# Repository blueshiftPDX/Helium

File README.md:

Helium
======

Helium supercapacitor-powered portable wireless speaker

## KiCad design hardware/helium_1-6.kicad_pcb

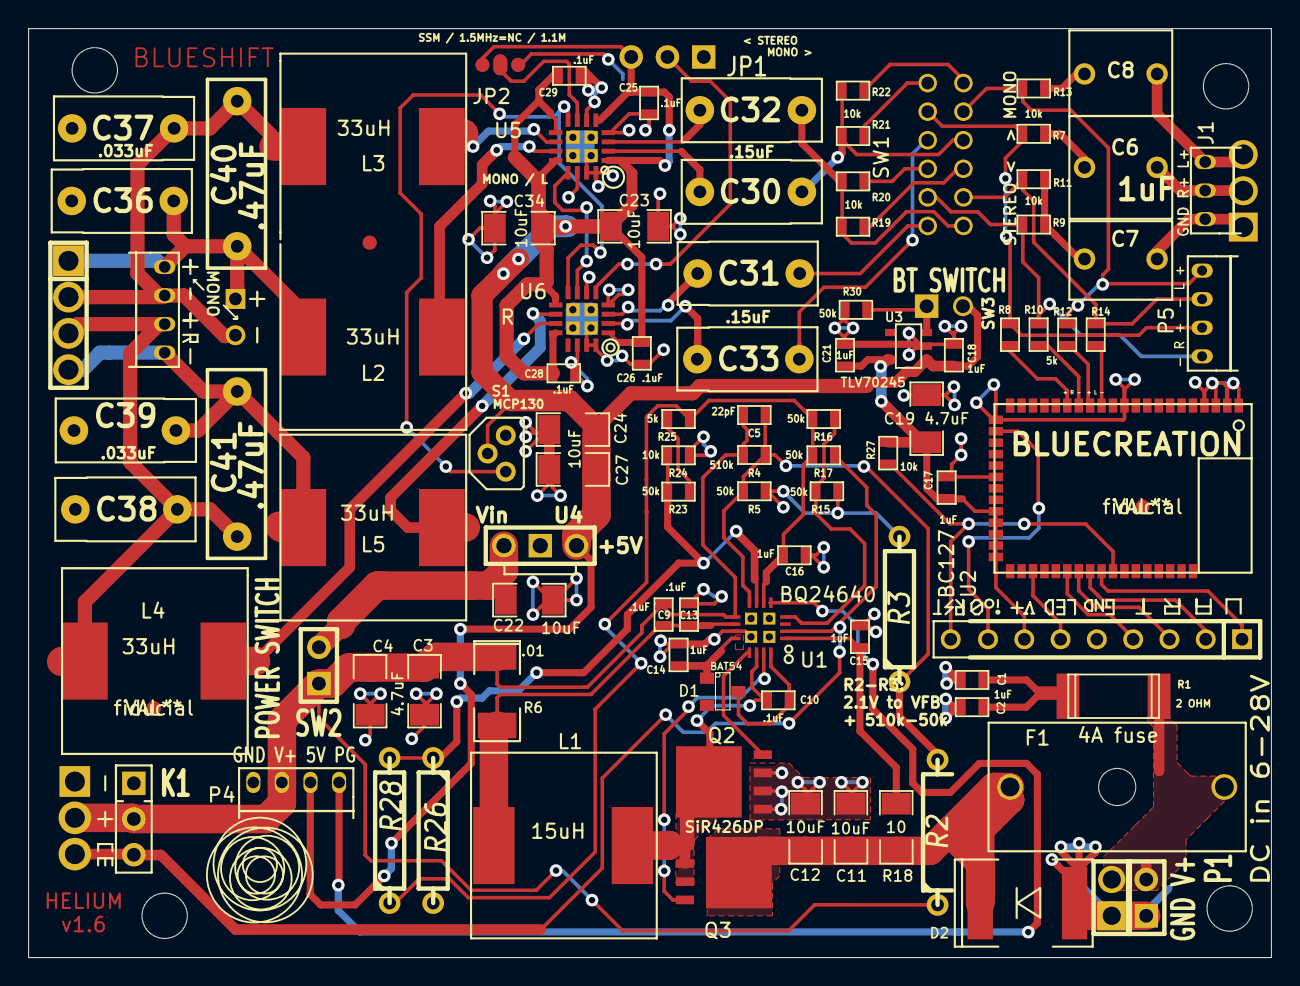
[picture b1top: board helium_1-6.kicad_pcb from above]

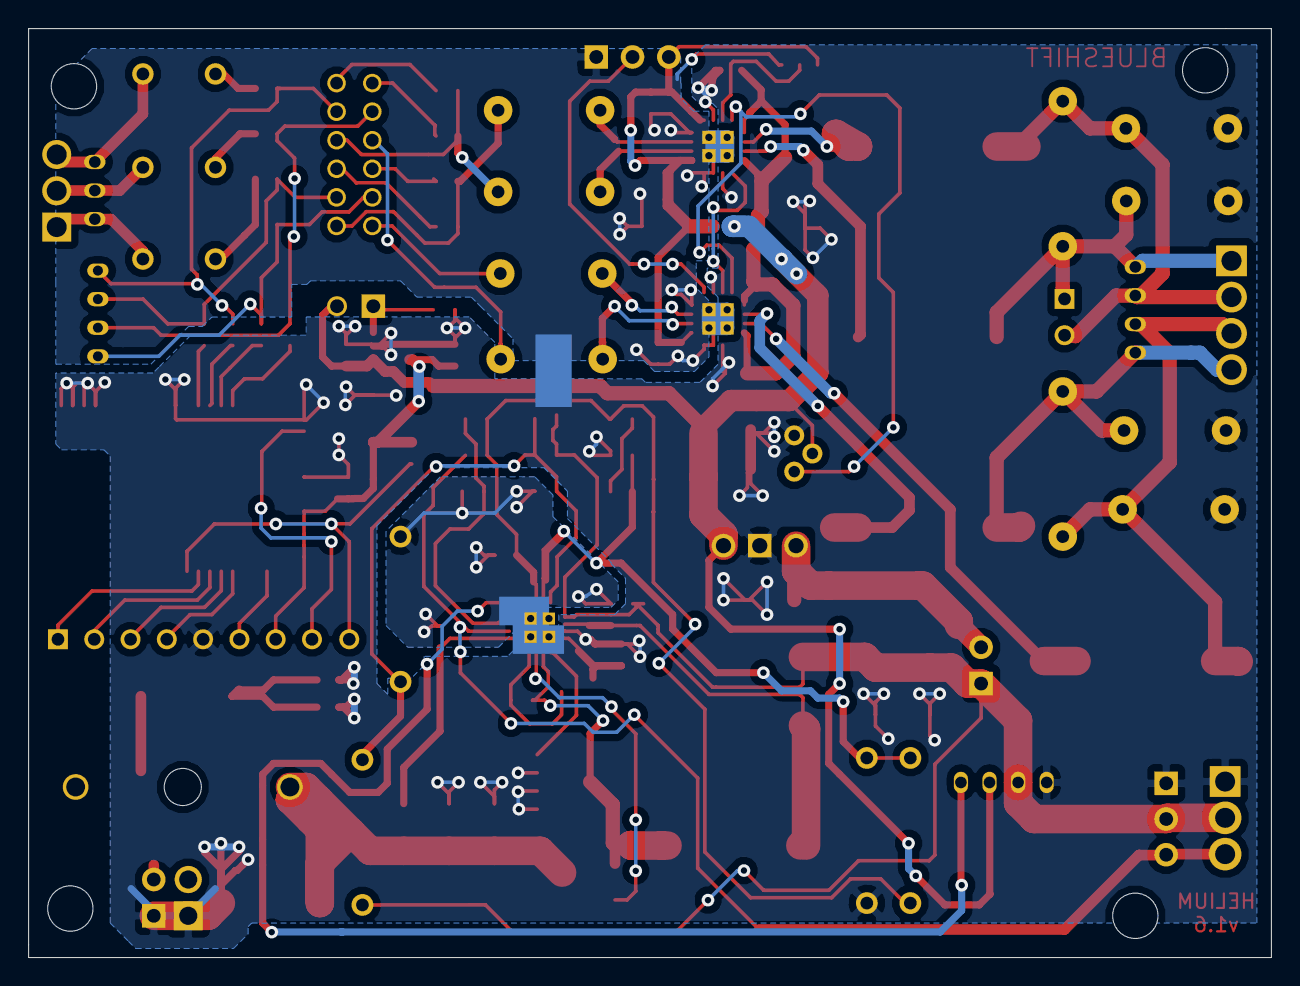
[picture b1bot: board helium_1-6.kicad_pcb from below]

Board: 2 copper layers, 87.0 x 65.0 mm, 112 parts (2 on the bottom side), 69 nets.

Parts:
C1, C2, C14, C15, C16, C17, C18, C21: 1uF; SM0603
C3, C4, C19: 4.7uF; SM1206
C5: 22pF; SM0603
C6, C7, C8: 1uF; cnp_7mm_035holes
C9, C10, C13, C25, C26, C28, C29: .1uF; SM0603
C11, C12, C22, C23, C24, C27, C34: 10uF; SM1206
C30, C31, C32, C33: .15uF; cnp_10x4.5mm
C36, C37, C38, C39: .033uF; cnp_10x4.5mm
C40, C41: .47uF; cnp_13x4mm
D1: BAT54; SOT23
D2: 10A diode; SM2010
F1: 4A fuse; fuse
J1: GND R+ L+; h3_2mm
JP1: < STEREO; SIL-3
JP2: SSM / 1.5MHz=NC / 1.1M; jump
K1: TO SUPERCAPS: GND / V+ / CE; SIL-4
L1: 15uH; SRR1280 inductor
L2: 33uH; SRR1280_ind_outline
L3, L4, L5: 33uH; SRR1280 inductor
P1: GND V+; SIL-2
P2: 4xUART/GND/LED/V+/IO; SIL-8-outputs
P3, P5: CONN_4; h4_2mm
P4: GND V+ 5V PG; h4_2mm
Q2, Q3: SiR426DP; PowerPak SO-8 Single
R1: 2 OHM; r_2512
R2: 931k MONO ONLY; R4
R3, R26, R28: DNP; R4
R4: 510k; SM0603
R5, R15, R16, R17, R23, R30: 50k; SM0603
R6: .01; SM2010
R7, R9, R11, R13, R19, R20, R21, R22, R24, R27: 10k; SM0603
R8, R10, R12, R14, R25: 5k; SM0603
R18: 10; SM1206
S1: MCP130; TO92PN
SIL-2, SIL-2#2: Val**; SIL-2
SIL-3, SIL-3#2: Val**; SIL-3
SIL-4: Val**; SIL-4
SW1: STEREO < > MONO; 4PDT MMS42R
SW2: POWER SWITCH; SIL-2
SW3: BT SWITCH; SIL-2
U1: BQ24640; BQ24640 QFN16
U2: BC127; bC127
U3: TLV70245; SOT23-5
U4: U4; SIL-3
U5: MONO / L; max9759
U6: R; max9759
XXX1, XXX3: SHORT!
fiducial: VAL**; fiducial
fiducial#2, fiducial#3: VAL**; fiducial
hole: Val**; hole
hole#2, hole#3, hole#4: Val**; hole
xxx2: short; SHORT!

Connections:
CAPGND: C1.2, C2.2, C3.2, C4.2, C11.2, C12.2, C14.2, C17.2, C18.2, C19.2, C21.2, C22.2, C24.2, C27.2, C28.2, C29.2, C34.2, C36.2, C37.1, C38.2, C39.1, D2.1, K1.1, P1.2, P2.5, P4.1, Q2.1, Q2.2, Q2.3, R24.2, R26.2, R30.2, S1.3, SIL-2#2.2, SIL-3.1, U1.11, U2.1, U2.2, U2.3, U2.4, U2.11, U2.22, U2.27, U3.2, U4.2, U5.6, U5.14, U6.6, U6.14, XXX1.2, xxx2.1
CAPV+: C3.1, C4.1, C5.1, C9.2, K1.2, P4.2, R2.1, R4.1, R6.1, SIL-3.2, SW2.1, U1.9
CE: K1.3, R17.2, SIL-3.3, U1.2
GNDA: C13.2, C15.2, C16.2, C23.2, C25.2, C26.2, JP1.1, JP2.3, R3.2, R5.2, R15.2, U5.4, U5.15, U5.16, U6.4, U6.15, U6.16, XXX1.1, xxx2.2
unnamed: JP1.2, U6.5
unnamed: P2.1, U2.43
unnamed: R22.1, SW1.12
unnamed: P5.1, R9.2, R10.1, SW1.2
unnamed: P5.2, R7.2, R8.1, SW1.5
unnamed: R21.1, SW1.6
unnamed: P5.3, R11.2, R14.1, SW1.8
unnamed: R20.1, SW1.3
unnamed: R19.1, SW1.9
unnamed: R10.2, U2.15
unnamed: P2.2, U2.42
unnamed: P2.3, U2.41
unnamed: P2.4, U2.40
unnamed: P2.9, R27.1, U2.44
unnamed: R14.2, U2.13
unnamed: C6.1, J1.2, SIL-3#2.2
unnamed: R12.2, U2.14
unnamed: R8.2, U2.16
unnamed: P5.4, R12.1, R13.2, SW1.11
unnamed: C30.1, U5.2
unnamed: C32.1, U5.3
unnamed: C31.2, U6.3
unnamed: C33.2, U6.2
unnamed: C5.2, R2.2, R3.1, R4.2, R5.1, U1.8
unnamed: C10.2, D1.2, U1.16
unnamed: C14.1, D1.1, U1.12
unnamed: R15.1, R16.2, U1.4
unnamed: L2.1, U5.11
unnamed: L5.1, U6.10
unnamed: L4.1, U6.11
unnamed: U5.13, U6.7
unnamed: C22.1, SW2.2, U4.3
unnamed: C8.1, J1.3, SIL-3#2.3
unnamed: R23.1, R25.2
unnamed: R23.2, R24.1, R26.1, R28.2, U1.7
unnamed: C31.1, SW1.1
unnamed: F1.1, P1.1, R1.1, SIL-2#2.1
unnamed: P4.4, U1.5
unnamed: C7.2, R9.1, R11.1
unnamed: C7.1, J1.1, SIL-3#2.1
unnamed: C8.2, R13.1
unnamed: L3.1, U5.10
unnamed: C32.2, R19.2, R20.2, SW1.7
unnamed: C30.2, R21.2, R22.2, SW1.10
unnamed: C33.1, SW1.4
unnamed: C6.2, R7.1
unnamed: P2.6, U2.37
unnamed: P2.8, U2.23
unnamed: JP2.2, U5.7
unnamed: C23.1, C25.1, C26.1, JP1.3, JP2.1, S1.1, U5.1, U5.5, U5.8, U6.1, U6.8, XXX3.2
unnamed: C11.1, C12.1, D2.2, F1.2, Q3.5, Q3.6, Q3.7, Q3.8, R18.1
unnamed: C10.1, L1.1, Q2.5, Q2.6, Q2.7, Q2.8, Q3.1, Q3.2, Q3.3, U1.14
unnamed: Q3.4, U1.15
unnamed: C16.1, R16.1, R17.1, R25.1, R28.1, U1.6
unnamed: Q2.4, U1.13
unnamed: C1.1, C2.1, R1.2
unnamed: C15.1, R18.2, U1.1
unnamed: C18.1, C24.1, C27.1, C28.1, C29.1, C34.1, P4.3, S1.2, SW3.2, U3.1, U4.1, U5.9, U5.12, U6.9, U6.12, XXX3.1
unnamed: C36.1, C40.1, L2.2, P3.1, SIL-2.1, SIL-4.1
unnamed: C37.2, C40.2, L3.2, P3.2, SIL-2.2, SIL-4.2
unnamed: C9.1, C13.1, L1.2, R6.2, U1.10
unnamed: R30.1, SW3.1, U3.3
unnamed: C17.1, C19.1, C21.1, P2.7, R27.2, U2.30, U2.31, U2.32, U2.33, U2.34, U3.5
unnamed: C38.1, C41.1, L4.2, P3.3, SIL-4.3
unnamed: C39.2, C41.2, L5.2, P3.4, SIL-4.4

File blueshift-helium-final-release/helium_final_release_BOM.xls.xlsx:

BOM | Helium_main_1-6 | 41814.0
red | Do not install
yellow | changed part from v1.5
green | addition from v1.5
QTY | Reference | Part number | Manufacturer | Distributor No. | Description | Footprint | DNI? | link | NOTES
1.0 | U1 | BQ24640RVAR | TI | 296-27258-1-ND | supercapacitor charger IC | VQFN16 |  | http://www.digikey.com/product-detail/en/BQ24640RVAR/296-272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
3.0 | P3, P4, P5 | B4B-PH-K-S(LF)(SN) | JST | 455-1706-ND | 4pin JST connector | H4_2mm |  | http://www.digikey.com/product-detail/en/B4B-PH-K-S(LF)(SN)/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 | was side entry in 1.5 – now top entry, additional connector at P5. Mount so tha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
2.0 | U5, U6 | MAX9759ETE+ | Maxim | MAX9759ETE+-ND | Mono Class-D Amp | TQFN16 |  | http://www.digikey.com/product-detail/en/MAX9759ETE%2B/MAX97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
3.0 | SW3, SW2, P1 | 3-644456-2 | TE Connectivity | A31112-ND | Header open 2 pin .1” | SIL-2 |  | http://www.digikey.com/product-detail/en/3-644456-2/A31112-N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
2.0 | Q3,Q2 | SIR426DP-T1-GE3 | Vishay | SIR426DP-T1-GE3CT-ND | Mosfet N-CH 40V | PowerPak SO-8 Single |  | http://www.digikey.com/product-detail/en/SIR426DP-T1-GE3/SIR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
0.0 | K1 | B03B-XASK-1(LF)(SN)(P) | JST | 455-1990-nd | Header shrouded 3 pin 2.5mm | SIL-3 | DNI |  | removed since v1.5
1.0 | U4 | Murata OKAMI 7805 | Murata | OKI-78SR-5/1.5-W36-C | Okami 7805 replacement TH | SIL-3 |  | http://www.digikey.com/product-detail/en/OKI-78SR-5%2F1.5-W3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
1.0 | L1 | SRR1280-150M | Bourns Inc. | SRR1280-150MCT-ND | 15uH | SRR1280 inductor |  | http://www.digikey.com/product-detail/en/SRR1280-150M/SRR128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
4.0 | L2,L3,L4,L5 | SRR1280-330M | Bourns Inc. | SRR1280-330MCT-ND | 33uH | SRR1280 inductor |  | http://www.digikey.com/product-detail/en/SRR1280-330M/SRR128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
1.0 | U3 | TLV70245DBVT | TI | 296-30480-1-ND | 4.5V LDO | SOT23-5 |  | http://www.digikey.com/product-detail/en/TLV70245DBVT/296-30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
1.0 | D2 | S10A-TP | Micro Commercial Co. | S10A-TPMSCT-ND | 10A diode | 2 pads .19” spacing |  | http://www.digikey.com/product-detail/en/S10A-TP/S10A-TPMSCT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
1.0 | F1 | 6.4900001039E10 | Littlefuse | WK0011-ND | fuse holder | http://media.digikey.com/pdf/Catalog%20Drawings/Circuit%20Pr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 |  | http://www.digikey.com/product-detail/en/64900001039/WK0011-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
1.0 | D1 | BAT54 | Fairchild Semi | BAT54FSCT-ND | BAT54 schottkey diode | SOT23-3 |  | http://www.digikey.com/product-detail/en/BAT54/BAT54FSCT-ND/458928
1.0 | R6 | WSL2010R0100FEA18 | Vishay | WSLF-.01CT-ND | .01 ohm sense resistor | SM2010 |  | http://www.digikey.com/product-detail/en/WSL2010R0100FEA18/W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
3.0 | C4,C3,C19 | UMK316AB7475KL-T | Taiyo Yuden | 587-2994-1-ND | 4.7uF X7R | SM1206 |  | http://www.digikey.com/product-detail/en/UMK316AB7475KL-T/58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
7.0 | C34,C27,C22,C23,C24,C12,C11 | GMK316BJ106KL-T | Taiyo Yuden | 587-2484-1-ND | 10uF X5R | SM1206 |  | http://www.digikey.com/product-detail/en/GMK316BJ106KL-T/587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
1.0 | R18 | RC1206FR-0710RL | Yageo | 311-10.0FRCT-ND | 10 ohm 1/4W 1% film | SM1206 |  | http://www.digikey.com/product-detail/en/RC1206FR-0710RL/311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
11.0 | R21,R19,R20,R29,R22,R24,R27,R13,R9,R7,R11 | RC0603FR-0710KL | Yageo | 311-10.0KHRCT-ND | RES 10.0K OHM 1/10W 1% | SM0603 |  | http://www.digikey.com/product-detail/en/RC0603FR-0710KL/311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
7.0 | C29,C13,C9,C10,C25,C26,C28 | C1608X7R1H104K080AA | TDK | 445-1314-1-ND | 0.1uF X7R | SM0603 |  | http://www.digikey.com/product-detail/en/C1608X7R1H104K080AA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
8.0 | C16,C14,C18,C21,C17,C1,C2,C15 | GMK107BJ105KA-T | Taiyo Yuden | 587-1437-1-ND | 1uF X7R | SM0603 |  | http://www.digikey.com/product-detail/en/GMK107BJ105KA-T/587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
5.0 | R14,R12,R10,R8,R25 | MCR03ERTF4991 | Rohm Semi | RHM4.99KCFCT-ND | 5k 1% | SM0603 |  | http://www.digikey.com/product-detail/en/MCR03ERTF4991/RHM4.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
6.0 | R23,R5,R16,R15,R17,R30 | ERJ-3EKF4992V | panasonic | P49.9KHCT-ND | 50k 1% | SM0603 |  | http://www.digikey.com/product-detail/en/ERJ-3EKF4992V/P49.9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
1.0 | R4 | RC0603FR-07487KL | Yageo | 311-487KHRCT-ND | 487k 1% | SM0603 |  | http://www.digikey.com/product-detail/en/RC0603FR-07487KL/31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 | different value from 1.5
1.0 | C5 | CL10C220JB8NNNC | Samsung | 1276-1023-1-ND | 22pF ceramic | SM0603 |  | http://www.digikey.com/product-detail/en/CL10C220JB8NNNC/127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
1.0 | R1 | ERJ-1TYJ2R0U | panasonic | PT2.0XCT-ND | 2 ohm 5% | SM2512 |  | http://www.digikey.com/product-detail/en/ERJ-1TYJ2R0U/PT2.0X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
1.0 | J1 | JST_3-PIN_WITH_WIREOUTS | JST | PRT-09915 | 3pin JST connector 2mm | H3_2mm |  | https://www.sparkfun.com/products/9915 | moved slightly north from 1.5
4.0 | C36,C37,C39,C38 | ECQ-E2333KF | panasonic | EF2333-ND | 0.033µF TH polyester | cap_NP_7.5mm |  | http://www.digikey.com/product-detail/en/ECQ-E2333KF/EF2333-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
4.0 | C31,C33,C32,C30 | ECQ-V1154JM | panasonic | P4727-ND | .15uF TH polyester | cap_NP_9mm |  | http://www.digikey.com/product-detail/en/ECQ-V1154JM/P4727-N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
3.0 | C8,C7,C6 | ECQ-V1H105JL | panasonic | P4675-ND | 1uF TH polyester | cap_NP_9mm |  | http://www.digikey.com/product-detail/en/ECQ-V1H105JL/P4675-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
2.0 | C41,C40 | ECQ-E2474KB | panasonic | P10975-ND | .47uF TH polyester | cap_NP_12.5mm |  | http://www.digikey.com/product-detail/en/ECQ-E2474KB/P10975-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
1.0 | U2 | BC127 | Bluecreation |  | BC127 Bluetooth module | 51 pin module |  | http://bluecreation.com/product_info.php?products_id=38 | shipping from Blue Creation (UK) (may have arrived 6/24?)
1.0 | SW1 | MMS42 | Apem Inc. | 679-1858-ND | 4PDT switch | DIL12 (2mm P x 2.5mm W) |  | http://www.digikey.com/product-detail/en/MMS42/679-1858-ND/1799368
4.0 | R2,R3,R26,R28 | DNP |  |  | extra resistor slots |  | DNI |  | Add 931K resistor at R2 for 15.9V limit; without this VCAP(max) = 23.9V
1.0 | JP1 | EG1218 | E-Switch | EG1903-ND | SPDT switch | SIL-3 |  | http://www.digikey.com/product-detail/en/EG1218/EG1903-ND/101726
1.0 | J2 | MOLEX_.1”_2pin | Molex | PRT-09918 | 2 pin molex vertical connector | SIL-2 |  | https://www.sparkfun.com/products/9918 | added since 1.5
1.0 | W1 | Automotive Jumper | Molex | PRT-09923 | Automotive Jumper 2-wire | SIL-3 |  | https://www.sparkfun.com/products/9923 | added since 1.5, replaces K1. Black to square pad, red to center pad. Connect s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
1.0 | S1 | MCP130-475DI/TO | Microchip Technology | MCP130-475DI/TO-ND | IC SUPERVISOR 4.75V LOW TO92 | TO-92-3 |  | http://www.digikey.com/product-detail/en/MCP130-475DI%2FTO/M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 | added since 1.5

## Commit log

2016-01-26 changing to uncompressed version
2016-01-26 removing zipped files
2016-01-26 restructuring
